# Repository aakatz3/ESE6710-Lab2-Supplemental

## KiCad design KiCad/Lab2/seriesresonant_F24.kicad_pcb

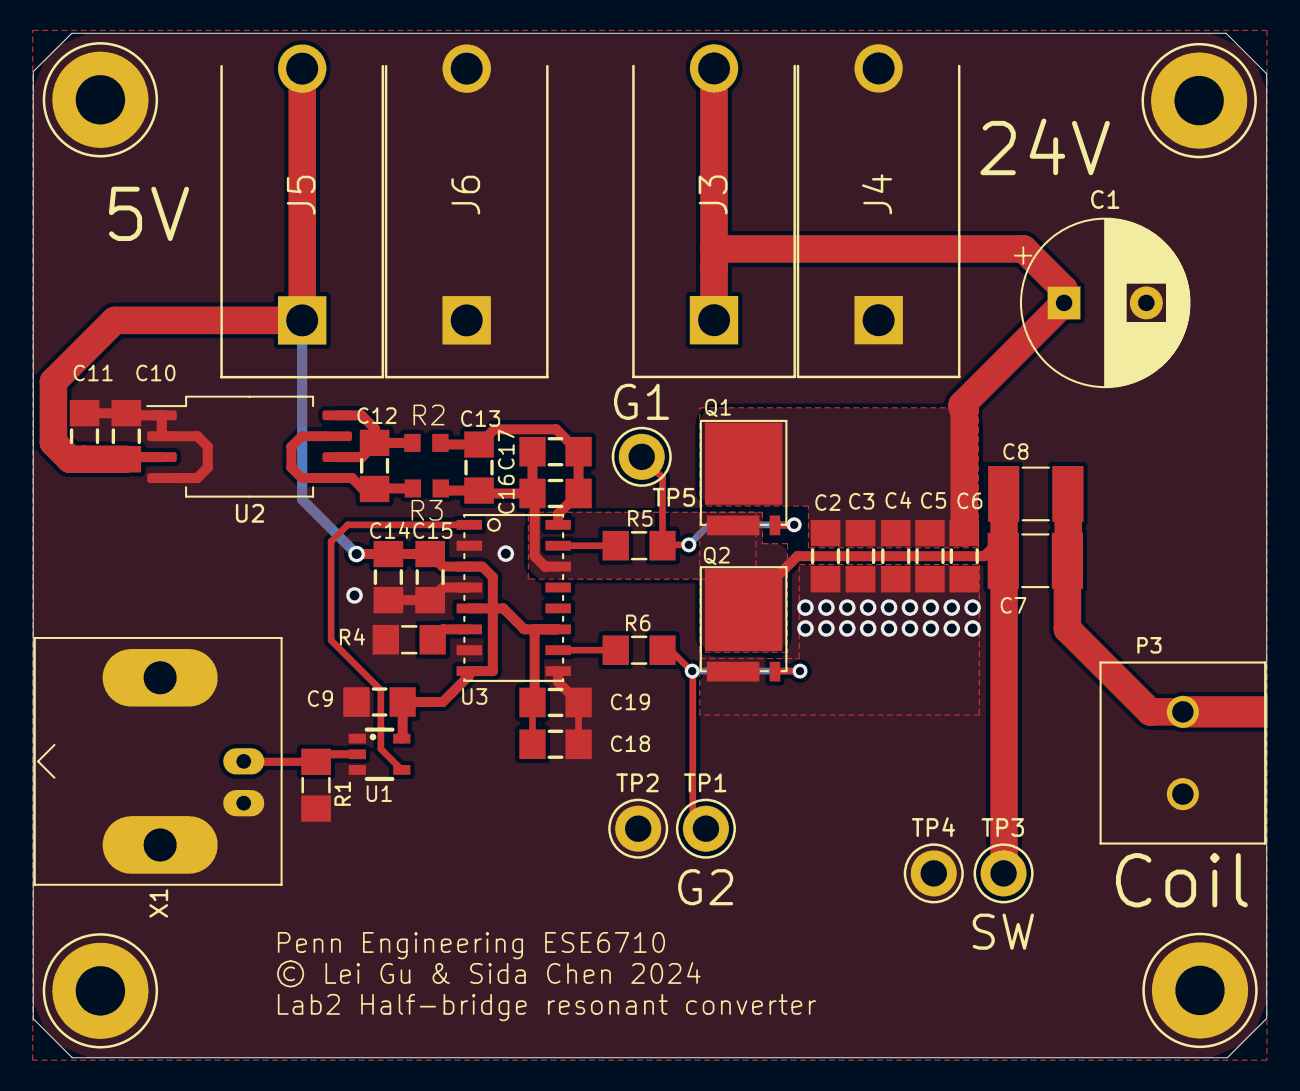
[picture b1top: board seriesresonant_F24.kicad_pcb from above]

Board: 2 copper layers, 75.0 x 62.3 mm, 45 parts (0 on the bottom side), 15 nets.

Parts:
C1: 100u; CP_Radial_D10.0mm_P5.00mm
C2, C3, C4, C5, C6, C10, C13, C14, C16, C18: 10u; C1206
C7, C8: CNP1812; C1812
C9: 0.1u; C1206
C11, C12, C15, C17, C19: .1u; C1206
H1, H2, H3, H4: MOUNT-PAD-ROUND3.0; 3,0-PAD
J3, J4, J5, J6: Conn_01x01_Pin; DELTRON_571-0500_0
P3: TERMINAL_BLOCK_17A
Q1, Q2: BSC065N06LS5; TDSON-8
R1: 1k; R1206
R2, R3: 1k5; R0603
R4, R5, R6: R1206
TP1, TP2, TP3, TP4, TP5: TestPoint_Probe; TestPoint_Keystone_5005-5009_Compact
U1: SN74LVC1G34; SOT-23(5)
U2: ADUM5028; SOIC-8_7.5x5.85mm_P1.27mm
U3: SI8274GB1-IS1; SOIC16NB
X1: BN35N61; BNC_Amphenol_B6252HB-NPP3G-50_Horizontal

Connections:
/5V: C9.1, C10.1, C11.1, C14.1, C15.1, C18.1, C19.1, J5.1, U1.5 (VCC), U2.3 (VDDP), U3.3 (VDDI), U3.5 (EN), U3.8 (VDDI), U3.11 (VDDB)
/5V_Q1: C13.1, C16.1, C17.1, R2.2, U3.16 (VDDA)
/5V_Q1_NF: C12.1, R2.1, U2.6 (VISO), U2.8 (VSEL)
/CR-LR: C7.2, C8.2, P3.1
/DT12: R4.1, U3.6 (DT)
/FS: R1.1, U1.2 (A), X1.1
/G1: Q1.G, R5.2, TP5.1
/G1_R: R5.1, U3.15 (VOA)
/G2: Q2.G, R6.2, TP1.1
/G2_R: R6.1, U3.10 (VOB)
/P1: U1.4 (Y), U3.1 (PWM)
/SW: C7.1, C8.1, C13.2, C16.2, C17.2, Q1.S, Q2.D, R3.2, TP3.1, U3.14 (GNDA)
/SW_NF: C12.2, R3.1, U2.5 (GNDISO1), U2.7 (GNDISO2)
/VIN: C1.1, C2.1, C3.1, C4.1, C5.1, C6.1, J3.1, Q1.D
GND: C1.2, C2.2, C3.2, C4.2, C5.2, C6.2, C9.2, C10.2, C11.2, C14.2, C15.2, C18.2, C19.2, H1.B3,0 (MOUNT), H2.B3,0 (MOUNT), H3.B3,0 (MOUNT), H4.B3,0 (MOUNT), J4.1, J6.1, P3.2, Q2.S, R1.2, R4.2, TP2.1, TP4.1, U1.1 (NC), U1.3 (GND), U2.1 (PDIS), U2.2 (GND1), U2.4 (GND2), U3.2 (NC1@1), U3.4 (GNDI), U3.7 (NC2@1), U3.9 (GNDB), X1.2

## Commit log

2025-12-30 Change remote

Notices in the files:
KiCad/Lab2/seriesresonant_F24.kicad_pcb:
© Lei Gu & Sida Chen 2024
